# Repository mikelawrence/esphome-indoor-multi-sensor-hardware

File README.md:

# ESPHome Indoor Multi-Sensor Hardware

<p align="center">

</p>

There are a lot of presence sensors using a combination of PIR and High Frequency Radar Human Presence Detectors to get a combination of quick response and low movement detection like when sleeping. Good examples of these types of sensor are the [Everything Presence One](https://shop.everythingsmart.io/products/everything-presence-one-kit) and [Roomsense IQ](https://www.roomsenselabs.com/). The later has a sensor module that you can add to support all sorts readings like Particular Matter (PM) Carbon Monoxide. But since I like to do everything myself. I started thinking about how I would approach this and more specifically what sensors did I want.

I settled on the following characteristics:

* ESP32-S3
* ESPHome software development
* USB-C Power
* Multiple options for Radar presence detection modules
  - Hi-Link LD2410B
  - Hi-Link LD2410S
  - Hi-Link LD2420
  - Hi-Link LD2450
  - DFRobot C4001 (SEN609 and SEN610)
* PIR (Panasonic)
* Sensirion SEN66 All-in-One (Package A)
  - Temperature
  - Humidity
  - Particulate Matter (PM) 
  - CO₂
  - Volatile Organic Compound (VOC)
  - Nitrogen Oxide (NOₓ)
* Or individual Sensors (Package B)
  - Sensirion SHT4X Temperature and Humidity
  - Sensirion SCD4X CO₂
  - Sensirion SGP4X VOC and NOₓ
* Bosch BMP581 Pressure
* Figaro TGS5141 Carbon Monoxide (CO)
* AMS TSL2591 Light
* Microphone for sound levels
* A Speaker for alerts
* INA228 Power and Energy Monitor

## Status
* **Rev -:** Has been fabricated and tested. I had JLCPCB fabricate the boards and I self assembled using a Home-Brew reflow oven by [Whizoo Controleo3](https://whizoo.com/). All circuits have been tested and found to be operational. 
* **Rev A:** There was an issue with signal integrity on the I²C bus when communicating with the SEN66. To fix the problem I added stronger pullups and a new and dedicated I²C bus to the SEN66. Thus Rev A was born. This revision was never fabricated. But all my Rev - boards have been modified to Rev A.
* **Rev B:** Added support for the LD2410S/LD2420 Radars, CO temperature sensor and INA238 power monitors for 3.3V and 3.3VA. Removed Radar power control. Board has been fabricated and testing has begun.

## Design Decisions
### ESP32 and ESPHome
ESPHome is closely aligned with Home Assistant. In fact they are the same company. Home Assistant uses ESPHome for some of their hardware like the [Home Assistant Voice Preview Edition](https://www.home-assistant.io/voice-pe/) or [Bluetooth Proxy](https://esphome.io/components/bluetooth_proxy.html). I chose a newer ESP32-S3 for this design which also has Bluetooth support.

This project uses ESP32-S3-WROOM-2-N32R16V which has an enormous 32MB of flash and 16MB of octal PSRAM. These specs are way out of the normal range for an ESP32, so why? First I wanted to be able to store sounds directly on the unit itself mainly so it can sound out alerts even if Home Assistant is not connected. The PSRAM came along with the big Flash but it also has benefits. Sound pressure analysis likes more PSRAM and so does Bluetooth Proxying.

### Sensors
#### Radar based Human Presence Sensors
Three of the Hi-Link sensors (LS2410B, LD2420 and LD2450) are supported by ESPHome directly but the DFRobot C4001 and LD2410S are not directly supported. This project uses the LD2410 component without change. For the LD2450 I have created a config that allows you to specify an installation angle, handle coordinate transforms and all zone detection. I created (with help from the Internet) a nice Home Assistant Lovelace configuration to visualize the installation angle and zone [here](https://mikelawrence.github.io/esphome-indoor-multi-sensor-config/home-assistant.html) for the LD2450 Radar and the LD2410 Radar's Gate configuration. For the DFRobot C4001 Radar I wrote an ESPHome External Component and created a [Pull Request](https://github.com/esphome/esphome/pull/9810) to add it to ESPHome. However the DFRobot team has since started their own [Pull Request](https://github.com/esphome/esphome/pull/10675). I will add support for their Pull Request when it comes out of draft and works. There is a [Pull Request](https://github.com/esphome/esphome/pull/8486) for the LD2410S. I will add support soon for the LD2410S and LD2420 Radars.

#### Sensor choices
The [SEN66](https://sensirion.com/products/catalog/SEN66) may be an expensive sensor package but it does it all, Temperature, Humidity, PM, CO₂, VOC and NOₓ. A tiny fan is primarily used for measuring PM but it also moves air by the temperature and humidity sensors making them fairly responsive. I call this Package A. If you choose not use the SEN66 you can populate the Package B individual sensors ([SHT4X](https://sensirion.com/media/documents/33FD6951/67EB9032/HT_DS_Datasheet_SHT4x_5.pdf), [SCD4X](https://sensirion.com/media/documents/48C4B7FB/67FE0194/CD_DS_SCD4x_Datasheet_D1.pdf) and [SGP4X](https://sensirion.com/media/documents/A056FE9C/61E970C2/Sensirion_Flyer_Gas_Sensors_Web.pdf)) to get Temperature, Humidity, CO₂, VOC and NOₓ. The only thing missing is PM.

#### Carbon Monoxide
For some reason CO sensors are not as common as CO₂ sensors. Most are expensive and have short life spans. The  Figaro TGS5141 is inexpensive and has a 10-year life span but it isn't a nice all-in-one with I²C interface. You have to add a transimpedance amplifier and then digitize the analog signal. I chose to add an ADS1115 16-bit ADC right next to the transimpedance amplifier instead of running analog signal across the board to the questionable ESP32 built in ADC. The ADS1115 also a has true differential Programmable Gain Amplifier on the input. This reduces the CO sensor circuit complexity. This sensor is not going to be very accurate but detection of CO in even low levels is probably a reason for concern. So even if not a safety sensor it can help.

I verified the CO circuit using CO Bump Gas. It doesn't calibrate, but it will prove that the sensor responds to the presence of CO. I used a small upside down container on my outside bench with the sensor I wanted to test inside. Squirting some bump gas inside with the thin straw showed that 4 out of 5 sensors responded to the gas. The 5'th that didn't respond had a solder bridge between two pins on the transimpedance amplifier. A quick removal of the solder bridge fixed the non-functioning sensor.

Rev B adds a DS18S20 temperature sensor to the design for CO calibration. The intent is to glue it to the CO sensor and use that for temperature calibration instead of using the ambient temp or the SHT4X sensor on the other side of the board.

> [!WARNING]
> This CO sensor is not rated for safety nor is it particularly accurate. Use at your own risk! I still have UL listed (American) CO detectors as my main line of defense.

#### Pressure and Light
The [BMP581](https://www.bosch-sensortec.com/media/boschsensortec/downloads/datasheets/bst-bmp581-ds004.pdf) pressure sensor is primarily used as a barometric pressure sensor but it is sensitive enough for micro-pressure changes like when a door is closed. Pressure can also be used to compensate the CO₂ sensor in either the SEN6X or the SCD4X. Light is another measurement that may or may not be helpful but I included it. Keep in mind that this measurement is inside an enclosure thus has some significant limitations when it comes to accuracy.

#### Speaker and Microphone
The SEN66 takes up a lot of space so a small speaker is necessary. I choose a flat speaker from [Same Sky](https://www.sameskydevices.com/product/audio/speakers/miniature-(10-mm~40-mm)/cms-251437-24sp-x8) and started playing. My first attempts were pretty, flat, meaning these small speakers don't move a lot of air and in free space they have almost no volume. After doing some research it became clear, the speaker needs a enclosure. I was able to come up with a small 3D printed enclosure attached to the PCB itself. Man what a difference. This 2W speaker kicks some serious butt.

I threw in the microphone to measure sound levels. The intent is listen for noise as additional presence detection.

#### Power and Energy Monitor
The [INA228](https://www.ti.com/lit/ds/symlink/ina228.pdf) power and energy monitor can give instantaneous readings of voltage, current and power but it also measures energy over time (WHr).

### USB-C Power
The board does not use USB-C Power Delivery but I am expecting 5V @ 3A which is readily available for most USB-C Power Bricks. The PCB has the appropriate resistors on the CC pins which will request 5V @ 3A from a USB-C Power Brick. The board does not need anywhere close to 3A but peaks near 0.75A are possible so be careful using a USB 2.0 Power Brick with a 0.5A default current. Actual testing shows a 1W average for the Package A version and slightly less than 0.9W average for the Package B option as measured by the INA228. Quick calculations show about 8.1kWh/yr for Package A and 7.3kWh/yr for Package B. In Texas that is less than $1 per year. These number are for Rev -.

## Enclosure
<p align="center">
  
</p>

More information is in the enclosure [README](enclosure/README.md) file.

## Configuration
Click [here](https://mikelawrence.github.io/esphome-indoor-multi-sensor-config/) to go to the installation and configuration repository.

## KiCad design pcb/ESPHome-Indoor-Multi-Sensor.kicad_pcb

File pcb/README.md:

# ESPHome Indoor Multi-Sensor PCB

The PCB is designed in [KiCad](https://www.kicad.org/). Fabrication and is tuned toward [JCLPCB](https://jlcpcb.com/). I chose not to use JLCPCB for assembly because they had a hard time with some the parts I included in this design. When I had the boards fabricated I also had them panelize two PCBs and produce a stencil for both for the panelized boards.

* **Rev -**: Is currently being fabricated. 

## Schematic
<p align="center">
     <br />
    Schematic
</p>

### Do Not Populate (DNP) Notes
When you use the SEN66 from Sensirion you don't need to install discrete sensor components ```U11```, ```U12```, ```U16```, ```C29```, ```C29```, ```C30```, ```C31``` or ```C43```.

## Bill of Materials
<p align="center">
     <br />
    Interactive BOM
</p>

## PCB Info
* 4 layer to support an additional ground plane and signal layer to reduce plane interruptions on the outer layers.
* There has been an attempt thermally isolate the SHT4X Temperature and Humidity Sensor but there are no guarantees.
* Dimensions are 52.5mm X 59.7mm.
* Requires oven reflow or hot air to assemble most components.

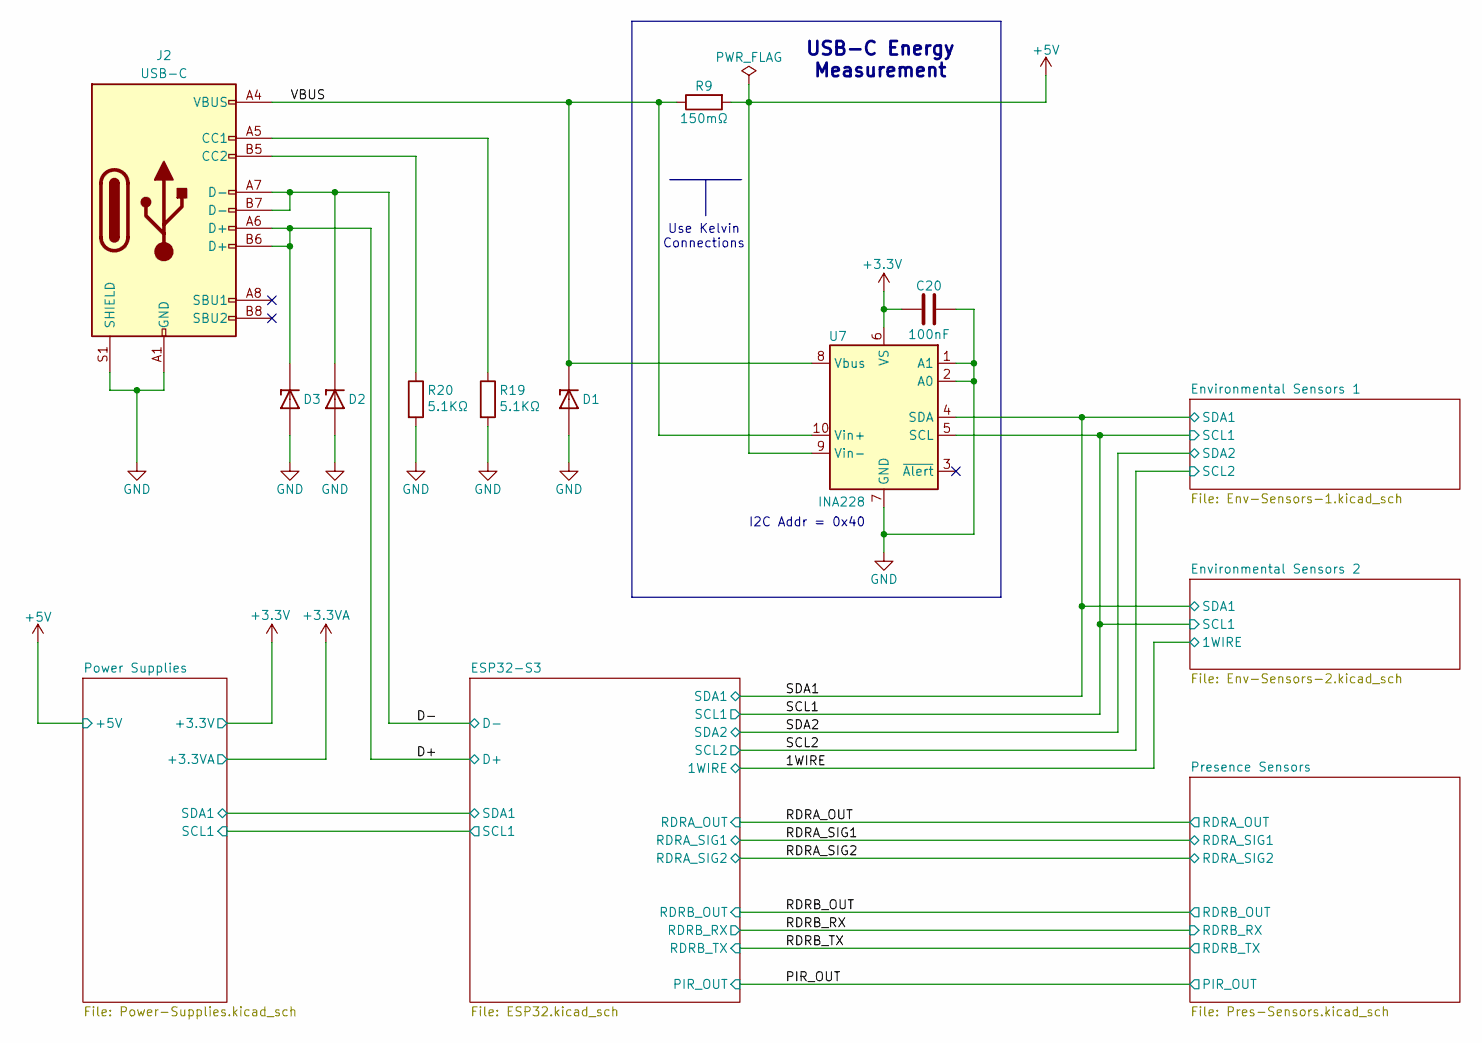
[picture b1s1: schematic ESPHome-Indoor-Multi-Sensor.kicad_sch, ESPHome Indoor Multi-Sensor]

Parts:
C20: 100nF; C_0402_1005Metric; Part Number CL05B104KB54PNC
D1, D2, D3: ESDA8P80-1U1M; TVS_ESDA25P35-1U1M; Part Number ESDA8P80-1U1M
J2: USB-C; USB_C_Receptacle_HRO_TYPE-C-31-M-12; Part Number 1332645
R9: 150mΩ; R_0805_2012Metric; Part Number WSL0805R1500FEA18
R19, R20: 5.1KΩ; R_0402_1005Metric; Part Number CRCW04025K10FKED
U7: INA228; VSSOP-10_3x3mm_P0.5mm; Part Number INA228AIDGSR

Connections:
+3.3V: C20.2, U7.6 (VS); also elsewhere on the board
+5V: R9.2, U7.9 (Vin-); also elsewhere on the board
/D+: D3.C, J2.A6 (D+), J2.B6 (D+); also elsewhere on the board
/D-: D2.C, J2.A7 (D-), J2.B7 (D-); also elsewhere on the board
/SCL1: U7.5 (SCL); also elsewhere on the board
/SDA1: U7.4 (SDA); also elsewhere on the board
/VBUS: D1.C, J2.A4 (VBUS), J2.A9 (VBUS), J2.B4 (VBUS), J2.B9 (VBUS), R9.1, U7.8 (Vbus), U7.10 (Vin+)
GND: C20.1, D1.A, D2.A, D3.A, J2.A1 (GND), J2.A12 (GND), J2.B1 (GND), J2.B12 (GND), J2.S1 (SHIELD), R19.2, R20.2, U7.1 (A1), U7.2 (A0), U7.7 (GND); also elsewhere on the board
unnamed: J2.A5 (CC1), R19.1
unnamed: J2.B5 (CC2), R20.1

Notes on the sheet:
I2C Addr = 0x40
USB-C Energy Measurement
Use Kelvin Connections

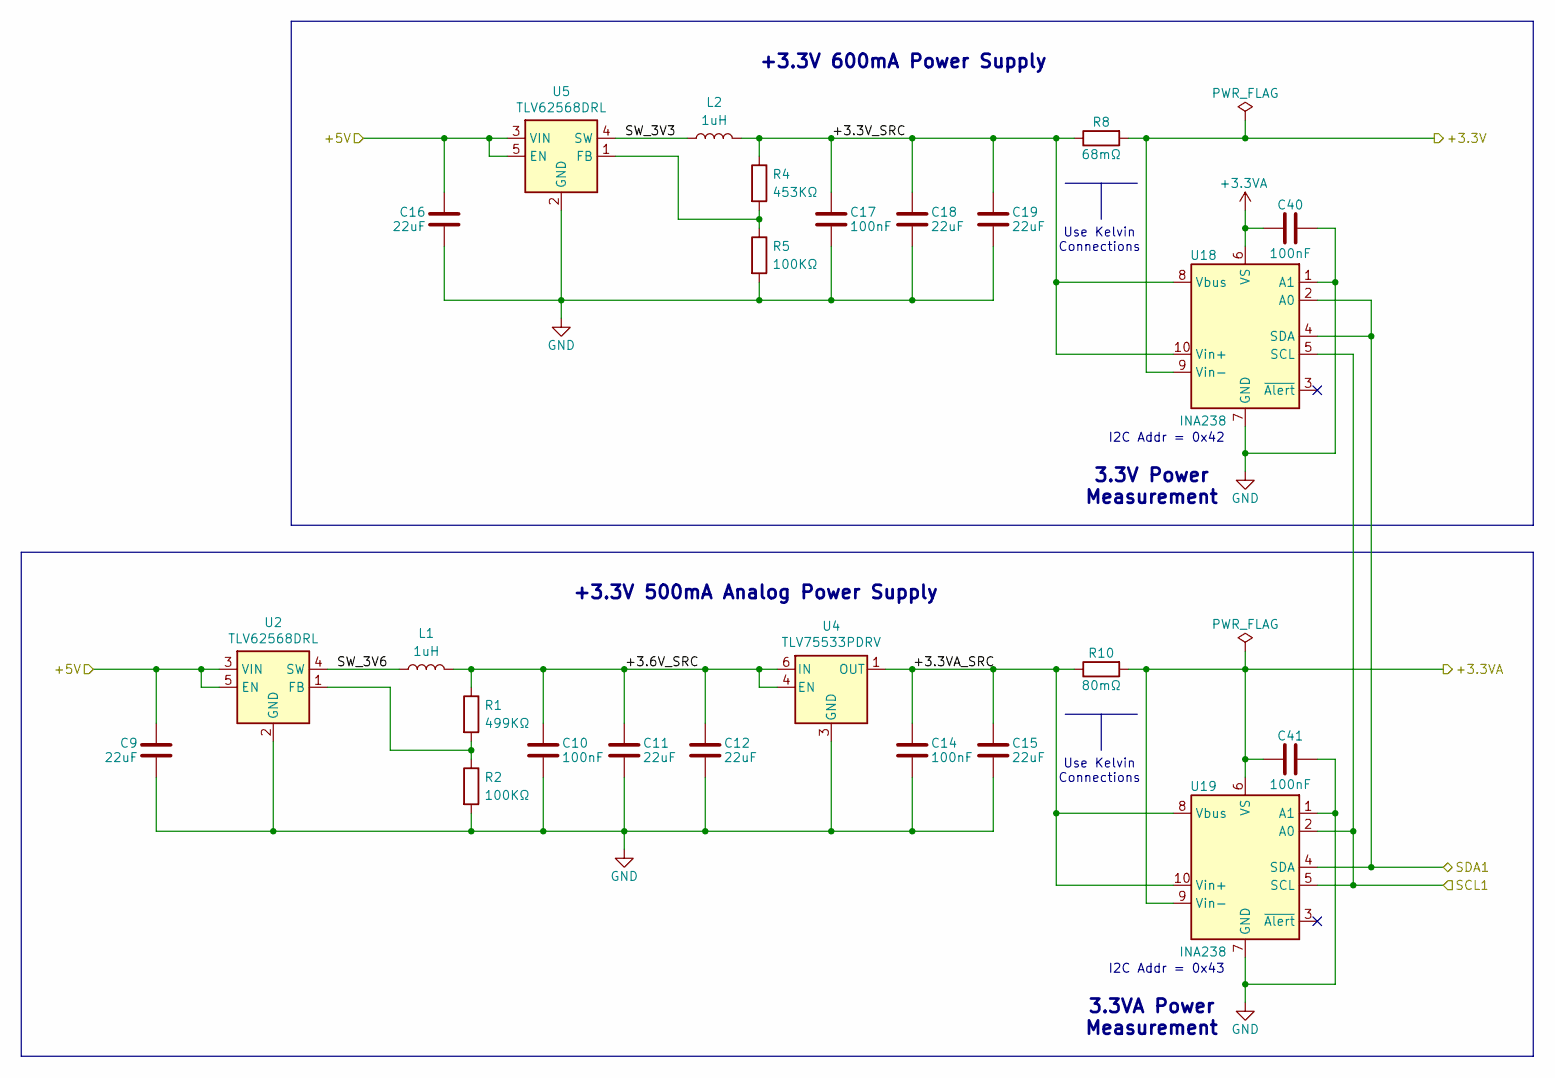
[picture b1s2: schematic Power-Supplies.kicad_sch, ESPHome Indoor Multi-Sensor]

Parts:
C9, C11, C12, C15, C16, C18, C19: 22uF; C_0603_1608Metric; Part Number GRM188R60J226MEA0D
C10, C14, C17, C40, C41: 100nF; C_0402_1005Metric; Part Number CL05B104KB54PNC
L1, L2: 1uH; L_1008_2520Metric; Part Number DFE252012F-1R0M=P2
R1: 499KΩ; R_0402_1005Metric; Part Number CRCW0402499KFKED
R2, R5: 100KΩ; R_0402_1005Metric; Part Number CRCW0402100KFKED
R4: 453KΩ; R_0402_1005Metric; Part Number CRCW0402453KFKED
R8: 68mΩ; R_0603_1608Metric; Part Number WSLP0603R0680FEA
R10: 80mΩ; R_0603_1608Metric; Part Number WSLP0603R0800FEB
U2, U5: TLV62568DRL; SOT50P160X60-6N; Part Number TLV62568DRL
U4: TLV75533PDRV; VREG_TLV75533PDRVR; Part Number TLV75533PDRV
U18, U19: INA238; VSSOP-10_3x3mm_P0.5mm; Part Number INA238AIDGSR

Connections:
+3.3V: R8.2, U18.9 (Vin-); also elsewhere on the board
+3.3VA: C40.2, C41.2, R10.2, U18.6 (VS), U19.6 (VS), U19.9 (Vin-); also elsewhere on the board
+5V: C9.1, C16.1, U2.3 (VIN), U2.5 (EN), U5.3 (VIN), U5.5 (EN); also elsewhere on the board
/Power Supplies/+3.3VA_SRC: C14.2, C15.1, R10.1, U4.1 (OUT), U19.8 (Vbus), U19.10 (Vin+)
/Power Supplies/+3.3V_SRC: C17.2, C18.1, C19.1, L2.2, R4.1, R8.1, U18.8 (Vbus), U18.10 (Vin+)
/Power Supplies/+3.6V_SRC: C10.2, C11.1, C12.1, L1.2, R1.1, U4.4 (EN), U4.6 (IN)
/Power Supplies/SW_3V3: L2.1, U5.4 (SW)
/Power Supplies/SW_3V6: L1.1, U2.4 (SW)
/SCL1: U18.5 (SCL), U19.2 (A0), U19.5 (SCL); also elsewhere on the board
/SDA1: U18.2 (A0), U18.4 (SDA), U19.4 (SDA); also elsewhere on the board
GND: C9.2, C10.1, C11.2, C12.2, C14.1, C15.2, C16.2, C17.1, C18.2, C19.2, C40.1, C41.1, R2.2, R5.2, U2.2 (GND), U4.3 (GND), U4.7 (GND), U5.2 (GND), U18.1 (A1), U18.7 (GND), U19.1 (A1), U19.7 (GND); also elsewhere on the board
unnamed: R1.2, R2.1, U2.1 (FB)
unnamed: R4.2, R5.1, U5.1 (FB)

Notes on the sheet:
+3.3V 600mA Power Supply
3.3VA Power Measurement
I2C Addr = 0x43
+3.3V 500mA Analog Power Supply
3.3V Power Measurement
Use Kelvin Connections
I2C Addr = 0x42

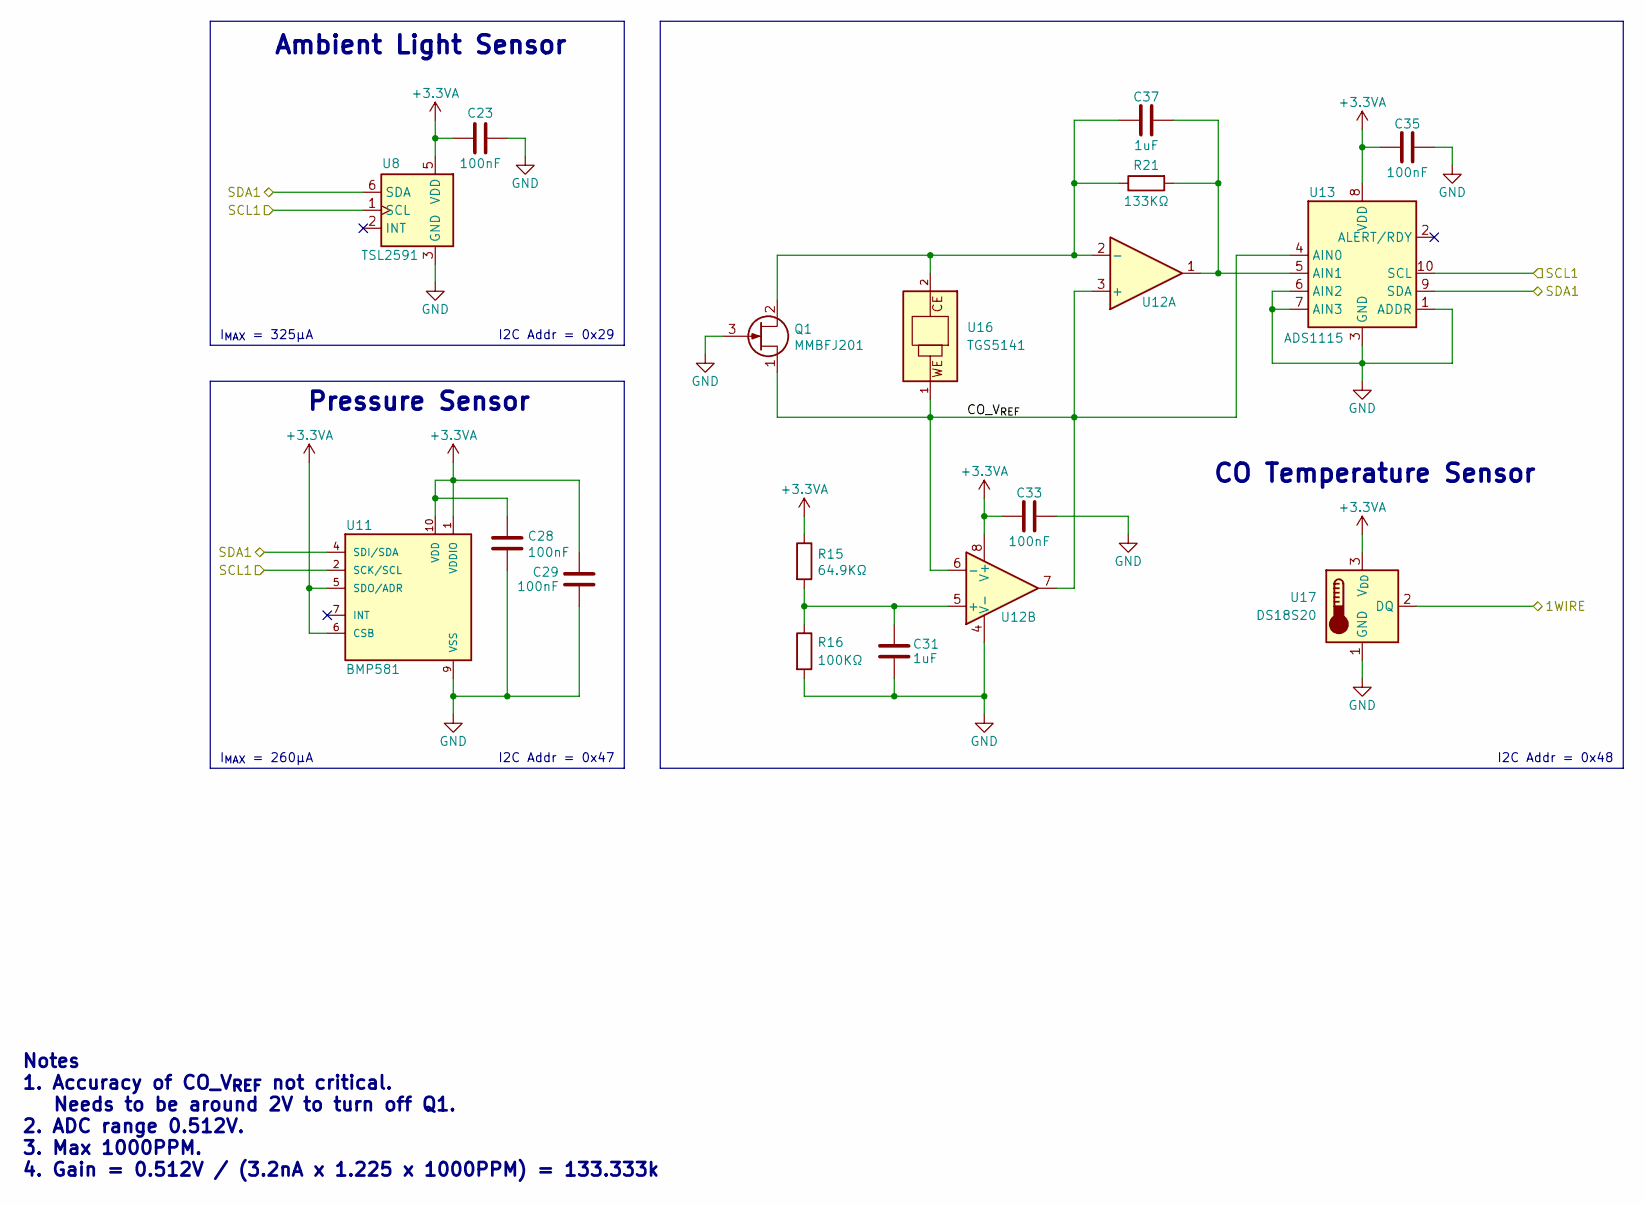
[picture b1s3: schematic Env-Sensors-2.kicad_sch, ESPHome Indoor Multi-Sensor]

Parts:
C23, C28, C29, C33, C35: 100nF; C_0402_1005Metric; Part Number CL05B104KB54PNC
C31, C37: 1uF; C_0402_1005Metric; Part Number CL05A105KA5NQNC
Q1: MMBFJ201; SOT-23; Part Number MMBFJ201
R15: 64.9KΩ; R_0402_1005Metric; Part Number CRCW040264K9FKED
R16: 100KΩ; R_0402_1005Metric; Part Number CRCW0402100KFKED
R21: 133KΩ; R_0402_1005Metric; Part Number CRCW0402133KFKED
U8: TSL2591; AMS_TSL25911FN; Part Number TSL2591
U11: BMP581; Part Number BMP581
U12: MCP6042; MSOP-8_3x3mm_P0.65mm; Part Number MCP6042T-I/MS
U13: ADS1115; TSSOP-10_3x3mm_P0.5mm; Part Number ADS1115IDGS
U16: TGS5141; TGS-5141; Part Number TGS5141-P00
U17: DS18S20; TO-92_Inline; Part Number DS18S20+

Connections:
+3.3VA: C23.2, C28.1, C29.1, C33.1, C35.1, R15.1, U8.5 (VDD), U11.1 (VDDIO), U11.5 (SDO/ADR), U11.6 (CSB), U11.10 (VDD), U12.8 (V+), U13.8 (VDD), U17.3 (V_{DD}); also elsewhere on the board
/1WIRE: U17.2 (DQ); also elsewhere on the board
/Environmental Sensors 2/CO_V_{REF}: Q1.1 (D), U12.3 (+), U12.6 (-), U12.7, U13.4 (AIN0), U16.1 (WE)
/SCL1: U8.1 (SCL), U11.2 (SCK/SCL), U13.10 (SCL); also elsewhere on the board
/SDA1: U8.6 (SDA), U11.4 (SDI/SDA), U13.9 (SDA); also elsewhere on the board
GND: C23.1, C28.2, C29.2, C31.2, C33.2, C35.2, Q1.3 (G), R16.2, U8.3 (GND), U11.3 (VSS), U11.8 (VSS), U11.9 (VSS), U12.4 (V-), U13.1 (ADDR), U13.3 (GND), U13.6 (AIN2), U13.7 (AIN3), U17.1 (GND); also elsewhere on the board
unnamed: C37.1, Q1.2 (S), R21.1, U12.2 (-), U16.2 (CE)
unnamed: C31.1, R15.2, R16.1, U12.5 (+)
unnamed: C37.2, R21.2, U12.1, U13.5 (AIN1)

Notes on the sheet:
I_{MAX} = 260µA
CO Temperature Sensor
I2C Addr = 0x29
I2C Addr = 0x48
Notes 1. Accuracy of CO_V_{REF} not critical. Needs to be around 2V to turn off Q1. 2. ADC range 0.512V. 3. Max 1000PPM. 4. Gain = 0.512V / (3.2nA x 1.225 x 1000PPM) = 133.333k
Ambient Light Sensor
I_{MAX} = 325µA
I2C Addr = 0x47
Pressure Sensor

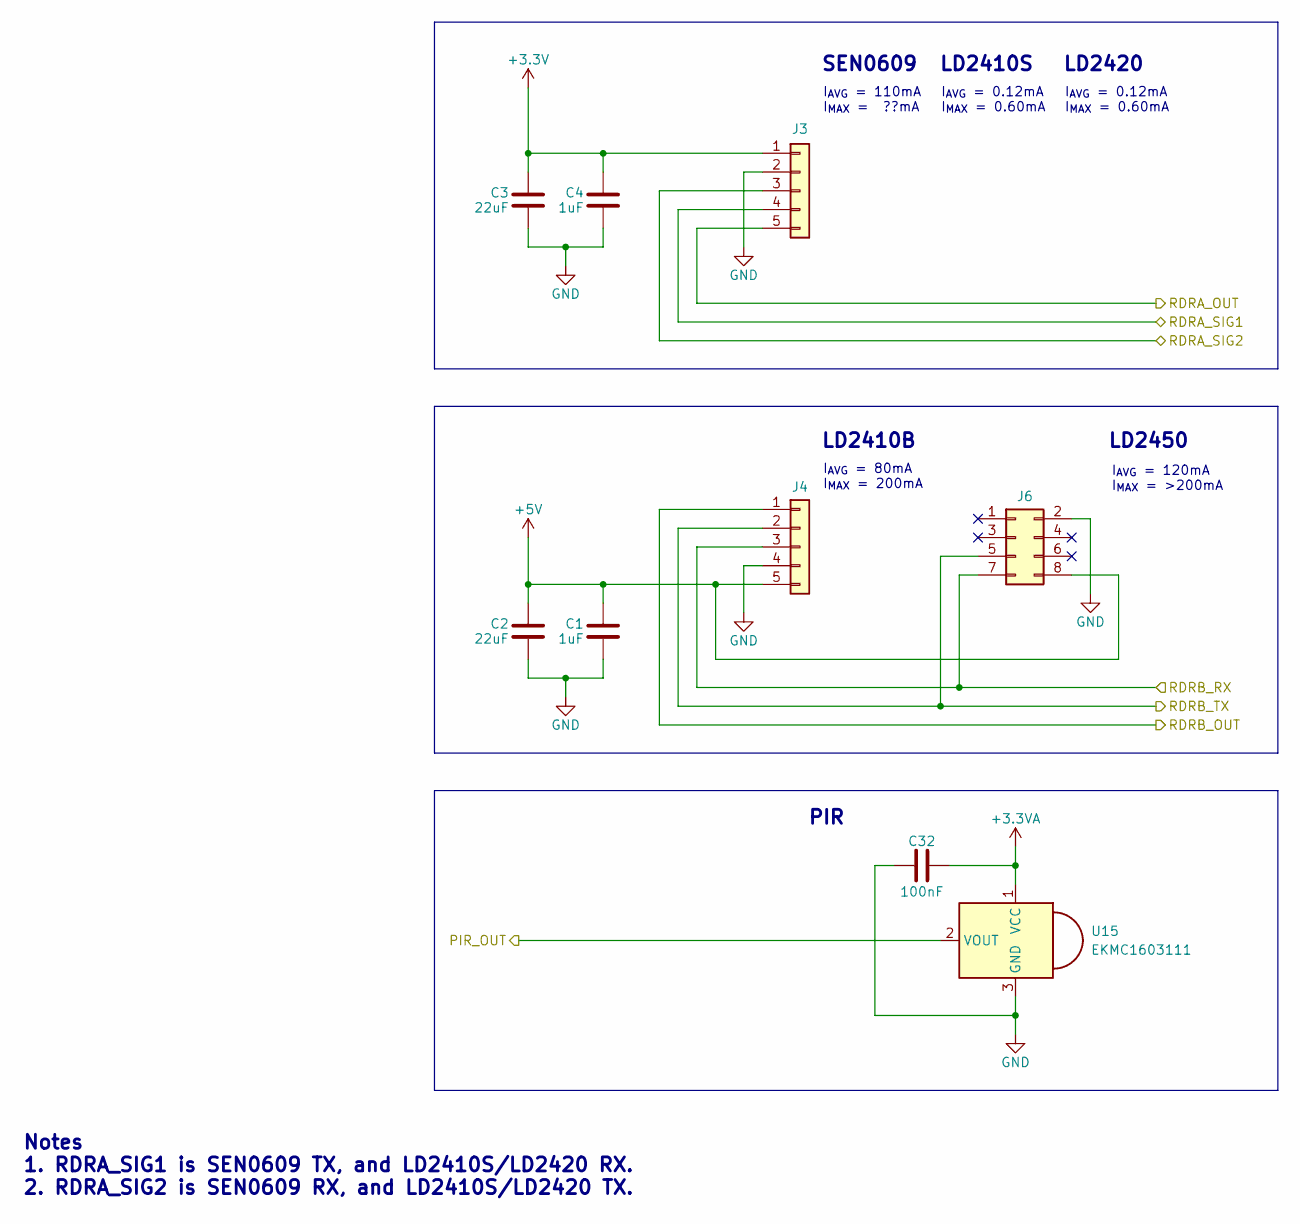
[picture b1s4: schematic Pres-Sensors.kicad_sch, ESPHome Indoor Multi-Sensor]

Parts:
C1, C4: 1uF; C_0402_1005Metric; Part Number CL05A105KA5NQNC
C2, C3: 22uF; C_0603_1608Metric; Part Number GRM188R60J226MEA0D
C32: 100nF; C_0402_1005Metric; Part Number CL05B104KB54PNC
J3: SEN0609; PinHeader_1x05_P2.54mm_Vertical; Part Number CES-105-01-T-S
J4: LD2410; PinSocket_1x05_P1.27mm_Vertical_SMD_Pin1Right; Part Number RSM-105-02-S-S
J6: LD2450; PinSocket_2x04_P2.00mm_Vertical_SMD; Part Number 79109-1003
U15: EKMC1603111; EKMC163111; Part Number EKMC1603111

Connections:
+3.3V: C3.1, C4.1, J3.1; also elsewhere on the board
+3.3VA: C32.2, U15.1 (VCC); also elsewhere on the board
+5V: C1.1, C2.1, J4.5, J6.8; also elsewhere on the board
/PIR_OUT: U15.2 (VOUT); also elsewhere on the board
/RDRA_OUT: J3.5; also elsewhere on the board
/RDRA_SIG1: J3.4; also elsewhere on the board
/RDRA_SIG2: J3.3; also elsewhere on the board
/RDRB_OUT: J4.1; also elsewhere on the board
/RDRB_RX: J4.3, J6.7; also elsewhere on the board
/RDRB_TX: J4.2, J6.5; also elsewhere on the board
GND: C1.2, C2.2, C3.2, C4.2, C32.1, J3.2, J4.4, J6.2, U15.3 (GND); also elsewhere on the board

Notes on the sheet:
I_{AVG} = 0.12mA I_{MAX} = 0.60mA
I_{AVG} = 110mA I_{MAX} = ??mA
LD2450
LD2410B
I_{AVG} = 80mA I_{MAX} = 200mA
PIR
LD2410S
LD2420
SEN0609
Notes 1. RDRA_SIG1 is SEN0609 TX, and LD2410S/LD2420 RX. 2. RDRA_SIG2 is SEN0609 RX, and LD2410S/LD2420 TX.
I_{AVG} = 120mA I_{MAX} = >200mA

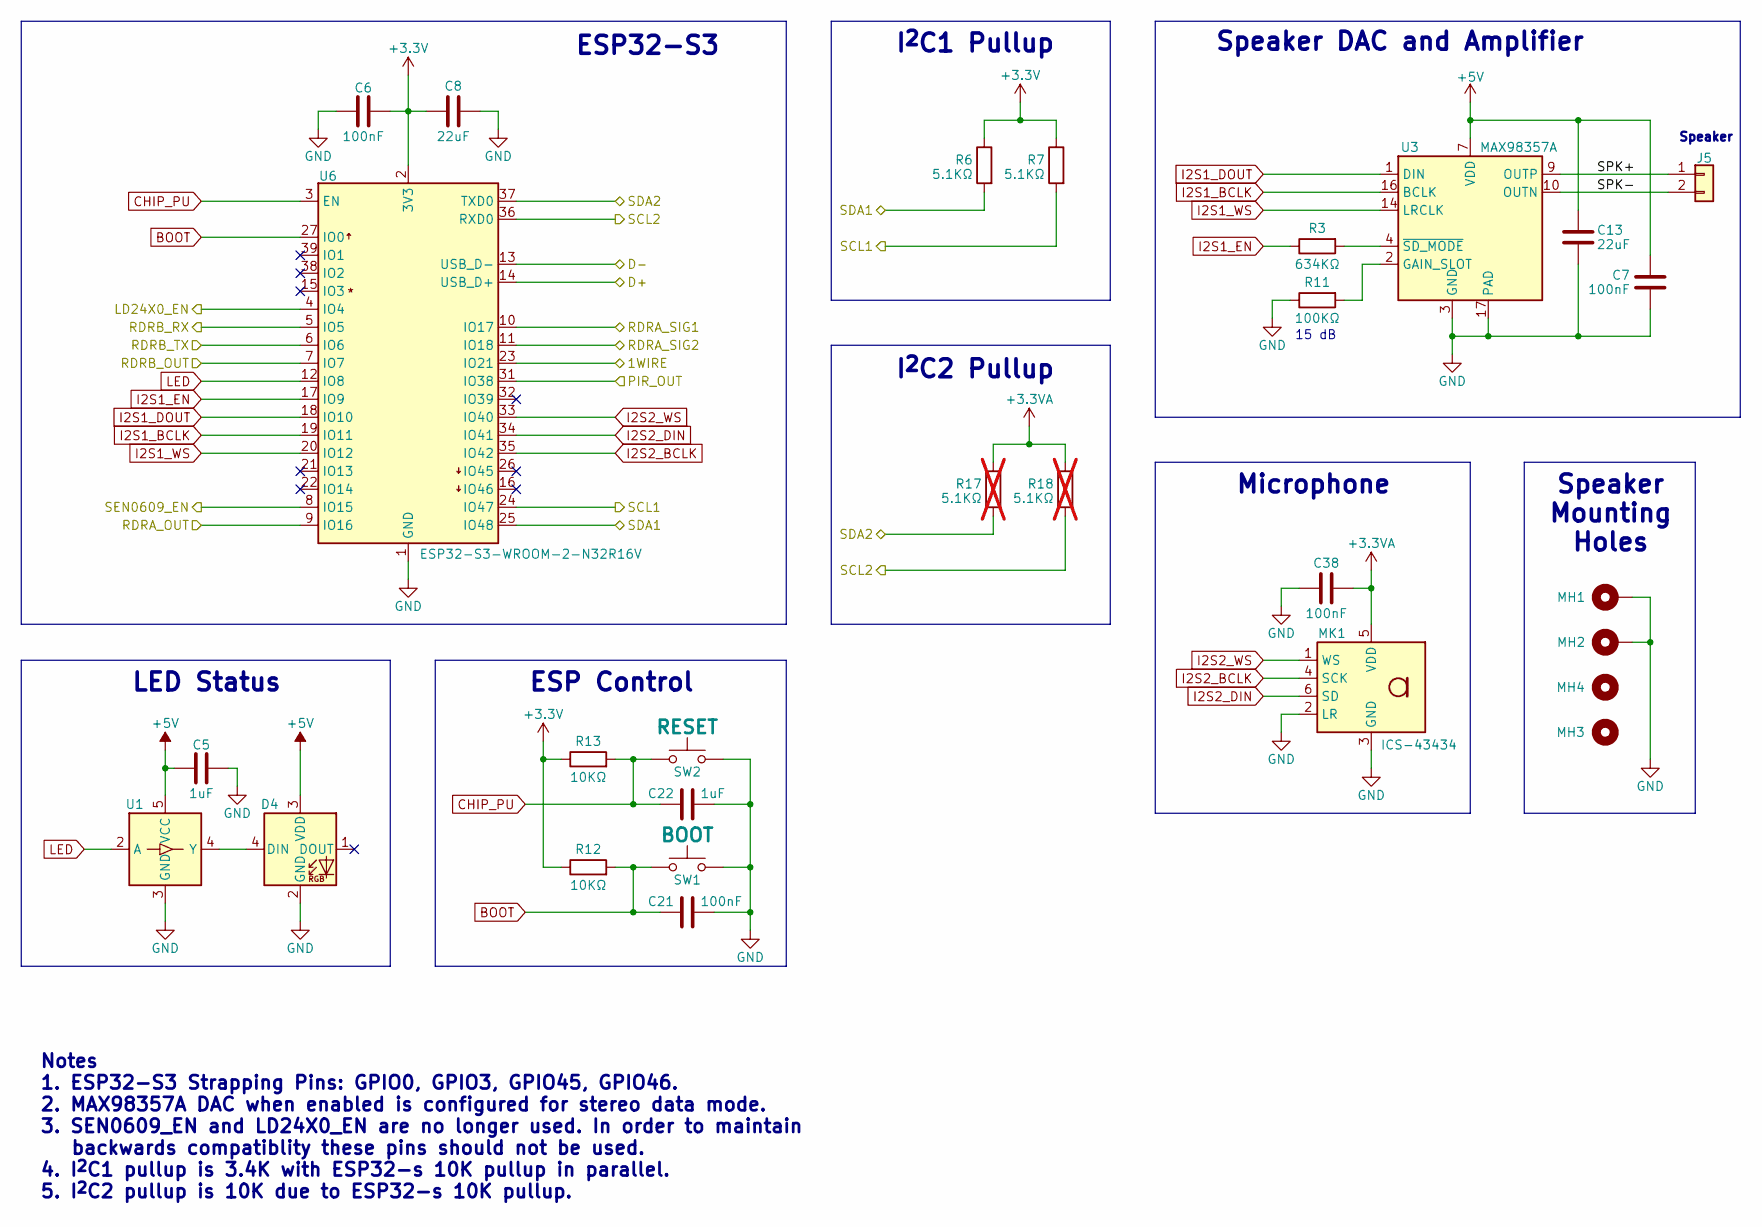
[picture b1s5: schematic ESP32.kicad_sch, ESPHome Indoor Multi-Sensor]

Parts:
C5, C22: 1uF; C_0402_1005Metric; Part Number CL05A105KA5NQNC
C6, C7, C21, C38: 100nF; C_0402_1005Metric; Part Number CL05B104KB54PNC
C8, C13: 22uF; C_0603_1608Metric; Part Number GRM188R60J226MEA0D
D4: NeoPixel_THT; LED_D5.0mm-4_RGB; Part Number 1938
J5: SPKR; PinHeader_1x02_P2.00mm_Vertical; Part Number CMS-251437-24SP-X8
MH1, MH2, MH3, MH4: MountingHole_2.2mm_M2_Pad
MK1: ICS-43434; InvenSense_ICS-43434-6_3.5x2.65mm; Part Number ICS-43434
R3: 634KΩ; R_0402_1005Metric; Part Number CRCW0402634KFKED
R6, R7: 5.1KΩ; R_0402_1005Metric; Part Number CRCW04025K10FKED
R11: 100KΩ; R_0402_1005Metric; Part Number CRCW0402100KFKED
R12, R13: 10KΩ; R_0402_1005Metric; Part Number CRCW040210K0FKED
R17, R18: 5.1KΩ; R_0402_1005Metric; Part Number CRCW04025K10FKED; not fitted
SW1: BOOT; SW_SPST_B3U-1000P-B; Part Number B3U-1000P
SW2: RESET; SW_SPST_B3U-1000P-B; Part Number B3U-1000P
U1: SN74LV1T34DBV; SOT-23-5; Part Number SN74LV1T34DBV
U3: MAX98357A; TQFN-16-1EP_3x3mm_P0.5mm_EP1.23x1.23mm; Part Number MAX98357AETE
U6: ESP32-S3-WROOM-2-N32R16V; ESP32-S3-WROOM-2; Part Number ESP32-S3-WROOM-2-N32R16V

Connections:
+3.3V: C6.2, C8.1, R6.1, R7.1, R12.1, R13.1, U6.2 (3V3); also elsewhere on the board
+3.3VA: C38.2, MK1.5 (VDD), R17.1, R18.1; also elsewhere on the board
+5V: C5.1, C7.1, C13.1, D4.3 (VDD), U1.5 (VCC), U3.7 (VDD), U3.8 (VDD); also elsewhere on the board
/1WIRE: U6.23 (IO21); also elsewhere on the board
/D+: U6.14 (USB_D+); also elsewhere on the board
/D-: U6.13 (USB_D-); also elsewhere on the board
/ESP32-S3/LD24X0_EN: U6.4 (IO4)
/ESP32-S3/SEN0609_EN: U6.8 (IO15)
/ESP32-S3/SPK+: J5.1, U3.9 (OUTP)
/ESP32-S3/SPK-: J5.2, U3.10 (OUTN)
/PIR_OUT: U6.31 (IO38); also elsewhere on the board
/RDRA_OUT: U6.9 (IO16); also elsewhere on the board
/RDRA_SIG1: U6.10 (IO17); also elsewhere on the board
/RDRA_SIG2: U6.11 (IO18); also elsewhere on the board
/RDRB_OUT: U6.7 (IO7); also elsewhere on the board
/RDRB_RX: U6.5 (IO5); also elsewhere on the board
/RDRB_TX: U6.6 (IO6); also elsewhere on the board
/SCL1: R7.2, U6.24 (IO47); also elsewhere on the board
/SCL2: R18.2, U6.36 (RXD0); also elsewhere on the board
/SDA1: R6.2, U6.25 (IO48); also elsewhere on the board
/SDA2: R17.2, U6.37 (TXD0); also elsewhere on the board
BOOT: C21.2, R12.2, SW1.2, U6.27 (IO0)
CHIP_PU: C22.1, R13.2, SW2.2, U6.3 (EN)
GND: C5.2, C6.1, C7.2, C8.2, C13.2, C21.1, C22.2, C38.1, D4.2 (GND), MH1.1, MH2.1, MK1.2 (LR), MK1.3 (GND), R11.1, SW1.1, SW2.1, U1.3 (GND), U3.3 (GND), U3.11 (GND), U3.15 (GND), U3.17 (PAD), U6.1 (GND), U6.40 (GND), U6.41 (GND); also elsewhere on the board
I2S1_BCLK: U3.16 (BCLK), U6.19 (IO11)
I2S1_DOUT: U3.1 (DIN), U6.18 (IO10)
I2S1_EN: R3.1, U6.17 (IO9)
I2S1_WS: U3.14 (LRCLK), U6.20 (IO12)
I2S2_BCLK: MK1.4 (SCK), U6.35 (IO42)
I2S2_DIN: MK1.6 (SD), U6.34 (IO41)
I2S2_WS: MK1.1 (WS), U6.33 (IO40)
LED: U1.2 (A), U6.12 (IO8)
unnamed: D4.4 (DIN), U1.4 (Y)
unnamed: R11.2, U3.2 (GAIN_SLOT)
unnamed: R3.2, U3.4 (~SD_MODE)

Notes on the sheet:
Speaker
I^{2}C2 Pullup
15 dB
ESP32-S3
Speaker Mounting Holes
I^{2}C1 Pullup
Notes 1. ESP32-S3 Strapping Pins: GPIO0, GPIO3, GPIO45, GPIO46. 2. MAX98357A DAC when enabled is configured for stereo data mode. 3. SEN0609_EN and LD24X0_EN are no longer used. In order to maintain backwards compatiblity these pins should not be used. 4. I^{2}C1 pullup is 3.4K with ESP32-s 10K pul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
Speaker DAC and Amplifier
ESP Control
Microphone
LED Status

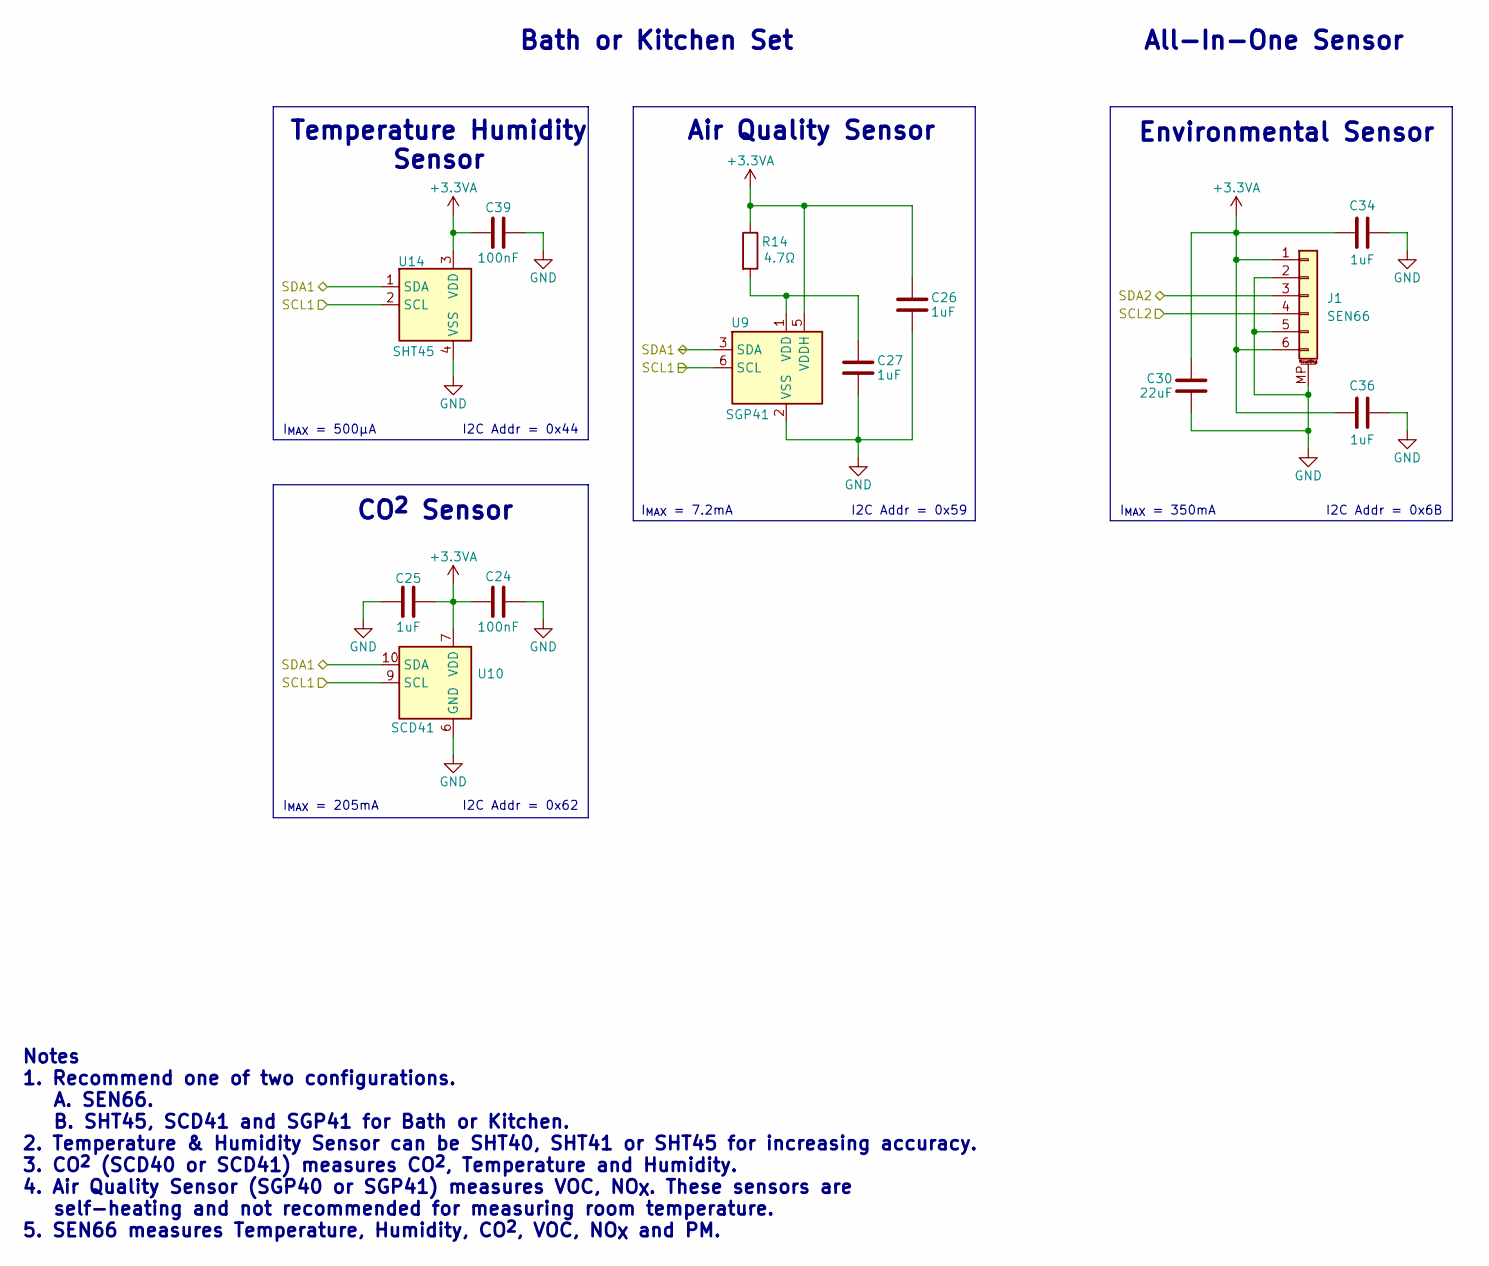
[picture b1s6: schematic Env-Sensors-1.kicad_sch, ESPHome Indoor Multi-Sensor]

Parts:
C24, C39: 100nF; C_0402_1005Metric; Part Number CL05B104KB54PNC
C25, C26, C27, C34, C36: 1uF; C_0402_1005Metric; Part Number CL05A105KA5NQNC
C30: 22uF; C_0603_1608Metric; Part Number GRM188R60J226MEA0D
J1: SEN66; JST_GH_BM06B-GHS-TBT_1x06-1MP_P1.25mm_Vertical; Part Number BM06B-GHS-TBT
R14: 4.7Ω; R_0402_1005Metric; Part Number CRCW04024R70FKED
U9: SGP41; XCDR_SGP40-D-R4; Part Number SGP41-D-R4
U10: SCD41; Sensirion_SCD4x-1EP_10.1x10.1mm_P1.25mm_EP4.8x4.8mm; Part Number SCD41-D-R2
U14: SHT45; Sensirion_DFN-4_1.5x1.5mm_P0.8mm_SHT4x_NoCentralPad; Part Number SHT45-AD1B-R2

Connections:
+3.3VA: C24.2, C25.2, C26.1, C30.1, C34.1, C36.1, C39.2, J1.1, J1.6, R14.1, U9.5 (VDDH), U10.7 (VDD), U10.19 (VDD), U14.3 (VDD); also elsewhere on the board
/SCL1: U9.6 (SCL), U10.9 (SCL), U14.2 (SCL); also elsewhere on the board
/SCL2: J1.4; also elsewhere on the board
/SDA1: U9.3 (SDA), U10.10 (SDA), U14.1 (SDA); also elsewhere on the board
/SDA2: J1.3; also elsewhere on the board
GND: C24.1, C25.1, C26.2, C27.2, C30.2, C34.2, C36.2, C39.1, J1.2, J1.5, J1.MP (MountPin), U9.2 (VSS), U9.4 (NA), U9.7 (EP), U10.6 (GND), U10.20 (GND), U10.21 (GND), U14.4 (VSS); also elsewhere on the board
unnamed: C27.1, R14.2, U9.1 (VDD)

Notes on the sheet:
I_{MAX} = 7.2mA
I2C Addr = 0x59
I2C Addr = 0x62
CO^{2} Sensor
Environmental Sensor
I_{MAX} = 350mA
Temperature Humidity Sensor
All-In-One Sensor
Bath or Kitchen Set
I2C Addr = 0x44
I2C Addr = 0x6B
I_{MAX} = 500µA
I_{MAX} = 205mA
Notes 1. Recommend one of two configurations. A. SEN66. B. SHT45, SCD41 and SGP41 for Bath or Kitchen. 2. Temperature & Humidity Sensor can be SHT40, SHT41 or SHT45 for increasing accuracy. 3. CO^{2} (SCD40 or SCD41) measures CO^{2}, Temperature and Humidity. 4. Air Quality Sensor (SGP40 or SGP41) 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
Air Quality Sensor
